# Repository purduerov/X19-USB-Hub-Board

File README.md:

# Purdue ROV X19 USB Hub Board

This board acts as both a PCIe-USB host controller and USB hub board for the ROV stack. In previous years, we had off-the-shelf USB hubs plugged in to the stock ports on the Raspberry Pi. We ran into multiple issues - there were bandwidth allocation issues with the default controller and the hub was just sitting on top of the stack in the enclosure.

The board uses a Renesas uPD720201 USB3.0 host controller to interface with the Raspberry Pi. That takes the PCIe 2.0 x1 interface and makes 4x USB 3.0 ports. Each of those ports (routed 2.0 since 3.0 bandwidth is not required) then go into a USB2422 hub controller and get split into 2 ports, for a total of 8 with 240 Mbps (30 MB/s) dedicated bandwidth.

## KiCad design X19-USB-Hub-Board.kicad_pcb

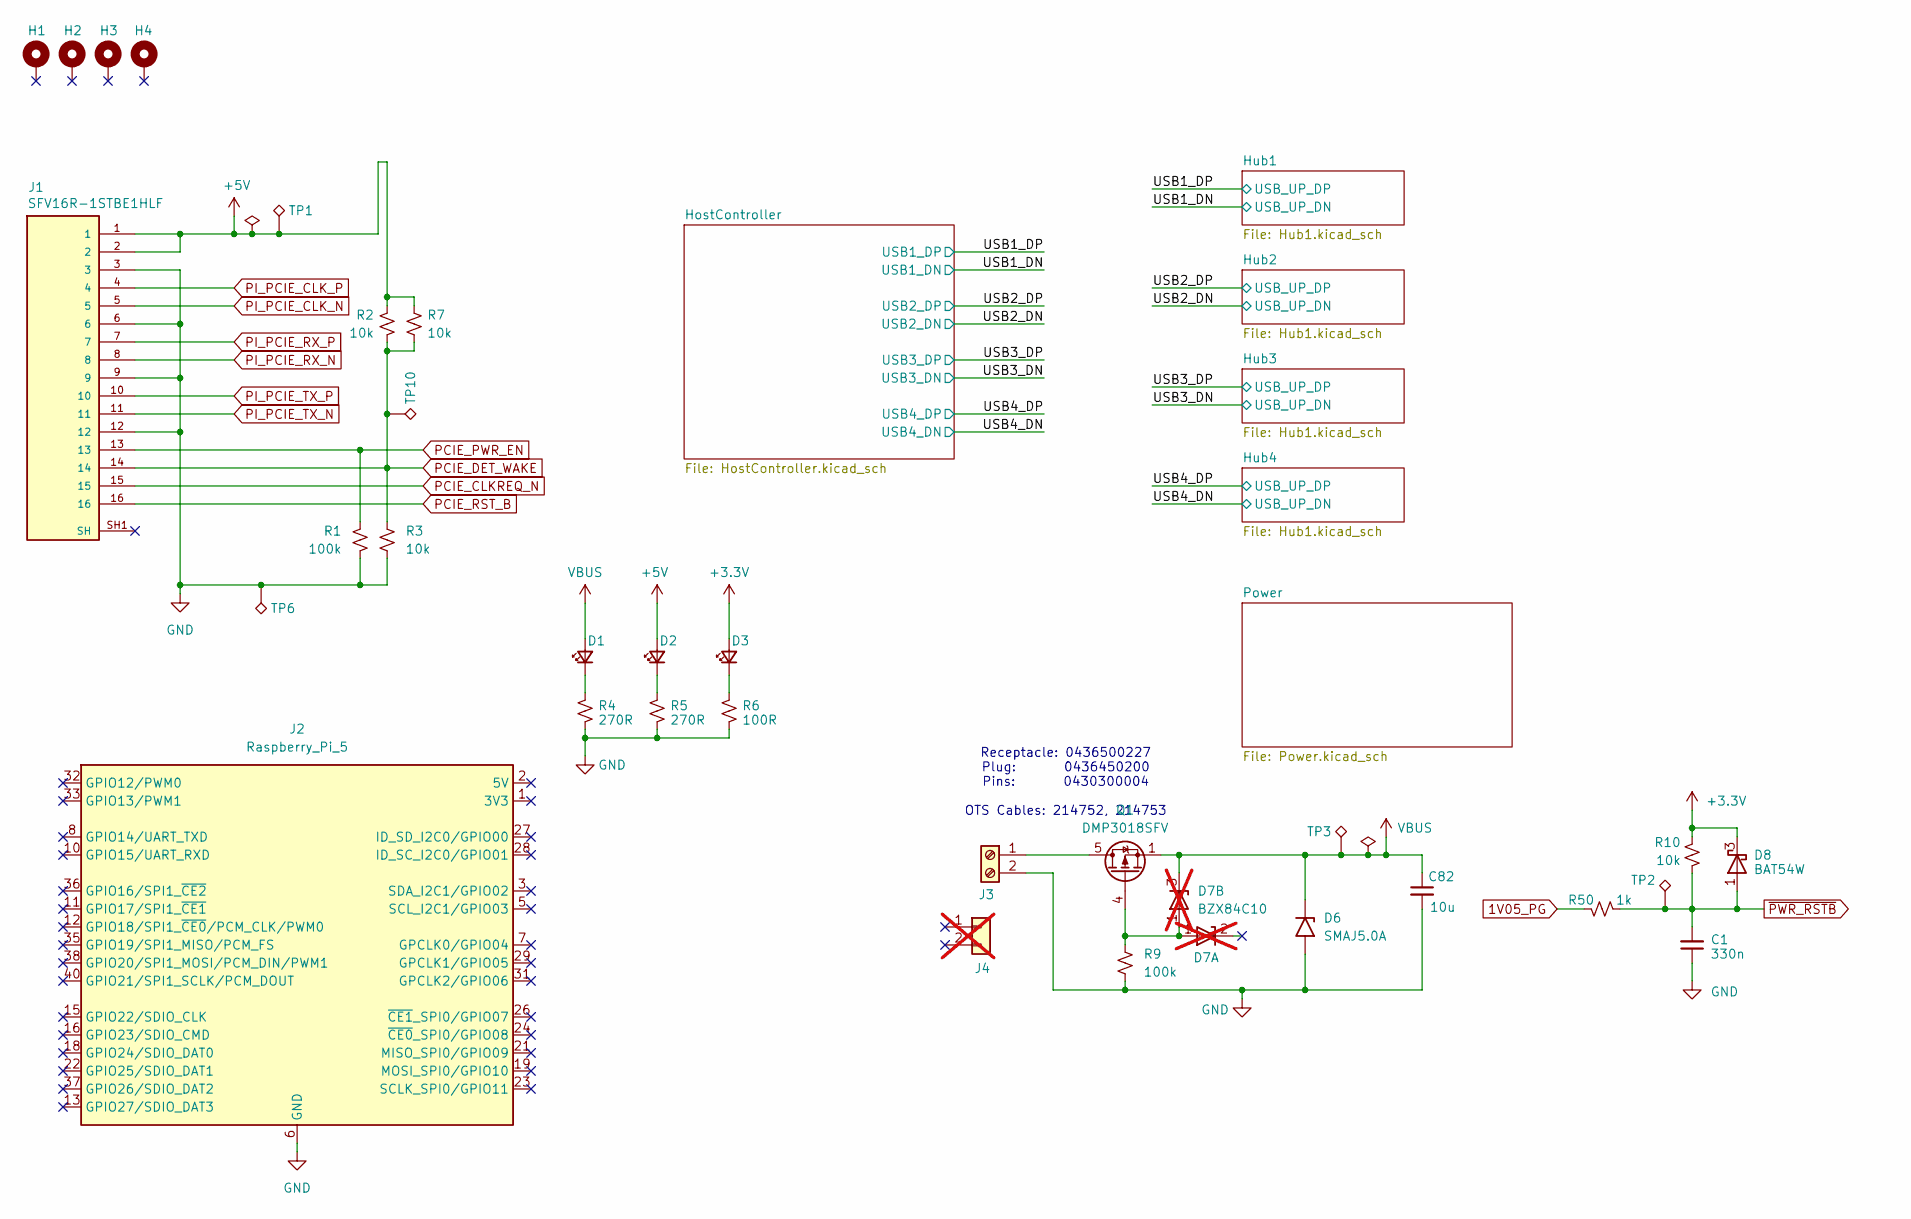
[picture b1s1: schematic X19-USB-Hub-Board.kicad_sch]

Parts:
C1: 330n; C_0402_1005Metric; Part Number CC0402KPX5R6BB334
C82: 10u; C_0805_2012Metric; Part Number CC0805KRX5R8BB106
D1, D2, D3: LED_Small; LED_0603_1608Metric; Part Number LTST-C190GKT
D6: SMAJ5.0A; D_SMA; Part Number SMAJ5.0A
D7: BZX84C10; SOT-23; Part Number BZX84C10; not fitted
D8: BAT54W; SOT-323_SC-70; Part Number BAT54WT-TP
H1, H2, H3, H4: MountingHole_Pad; MountingHole_2.7mm_M2.5_Pad
J1: SFV16R-1STBE1HLF; AMPHENOL_SFV16R-1STBE1HLF; PARTREV B; DigiKey 609-1786-1-ND
J2: Raspberry_Pi_5; PinSocket_2x20_P2.54mm_Vertical; Part Number 1528-1385-ND
J3: 0436500227; Part Number 0436500227
J4: 0436450200; Part Number 0436450200; not fitted
Q1: DMP3018SFV; Diodes_PowerDI3333-8; Part Number DMP3018SFV
R1, R9: 100k; R_0603_1608Metric; Part Number RC0603FR-07100KL
R2, R3, R7, R10: 10k; R_0402_1005Metric; Part Number RC0402FR-0710KL
R4, R5: 270R; R_0603_1608Metric; Part Number RC0603FR-07270RL
R6: 100R; R_0603_1608Metric; Part Number RC0603FR-07100RL
R50: 1k; R_0402_1005Metric; Part Number RC0402FR-071KL
TP1: 5V; TestPoint_Pad_D1.0mm
TP2: ~{PWR_RST}; TestPoint_Pad_D1.0mm
TP3: VBUS; TestPoint_Pad_D1.0mm
TP6: GND; TestPoint_Pad_D1.0mm
TP10: PCIE_DET_WAKE; TestPoint_Pad_D1.0mm

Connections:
1V05_PG: R50.1; also elsewhere on the board
+3.3V: D3.2 (A), D8.3 (K), R10.1; also elsewhere on the board
+5V: D2.2 (A), J1.1, J1.2, R2.1, R7.1, TP1.1 (1_1); also elsewhere on the board
GND: C1.1, C82.2, D6.2 (A2), J1.3, J1.6, J1.9, J1.12, J2.6 (GND), J2.9 (GND), J2.14 (GND), J2.20 (GND), J2.25 (GND), J2.30 (GND), J2.34 (GND), J2.39 (GND), J3.2, R1.2, R3.2, R4.1, R5.1, R6.1, R9.2, TP6.1 (1_1); also elsewhere on the board
unnamed: D1.1 (K), R4.2
unnamed: D2.1 (K), R5.2
unnamed: D3.1 (K), R6.2
unnamed: D7.1 (A), Q1.4 (G), R9.1
unnamed: J3.1, Q1.5 (D)
PCIE_CLKREQ_N: J1.15; also elsewhere on the board
PCIE_DET_WAKE: J1.14, R2.2, R3.1, R7.2, TP10.1 (1_1)
PCIE_PWR_EN: J1.13, R1.1; also elsewhere on the board
PCIE_RST_B: J1.16; also elsewhere on the board
PI_PCIE_CLK_N: J1.5; also elsewhere on the board
PI_PCIE_CLK_P: J1.4; also elsewhere on the board
PI_PCIE_RX_N: J1.8; also elsewhere on the board
PI_PCIE_RX_P: J1.7; also elsewhere on the board
PI_PCIE_TX_N: J1.11; also elsewhere on the board
PI_PCIE_TX_P: J1.10; also elsewhere on the board
VBUS: C82.1, D1.2 (A), D6.1 (A1), D7.3 (K), Q1.1 (S), Q1.2 (S), Q1.3 (S), TP3.1 (1_1); also elsewhere on the board
~PWR_RSTB: C1.2, D8.1 (A), R10.2, R50.2, TP2.1 (1_1); also elsewhere on the board

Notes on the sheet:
Receptacle: 0436500227 Plug: 0436450200 Pins: 0430300004 OTS Cables: 214752, 214753

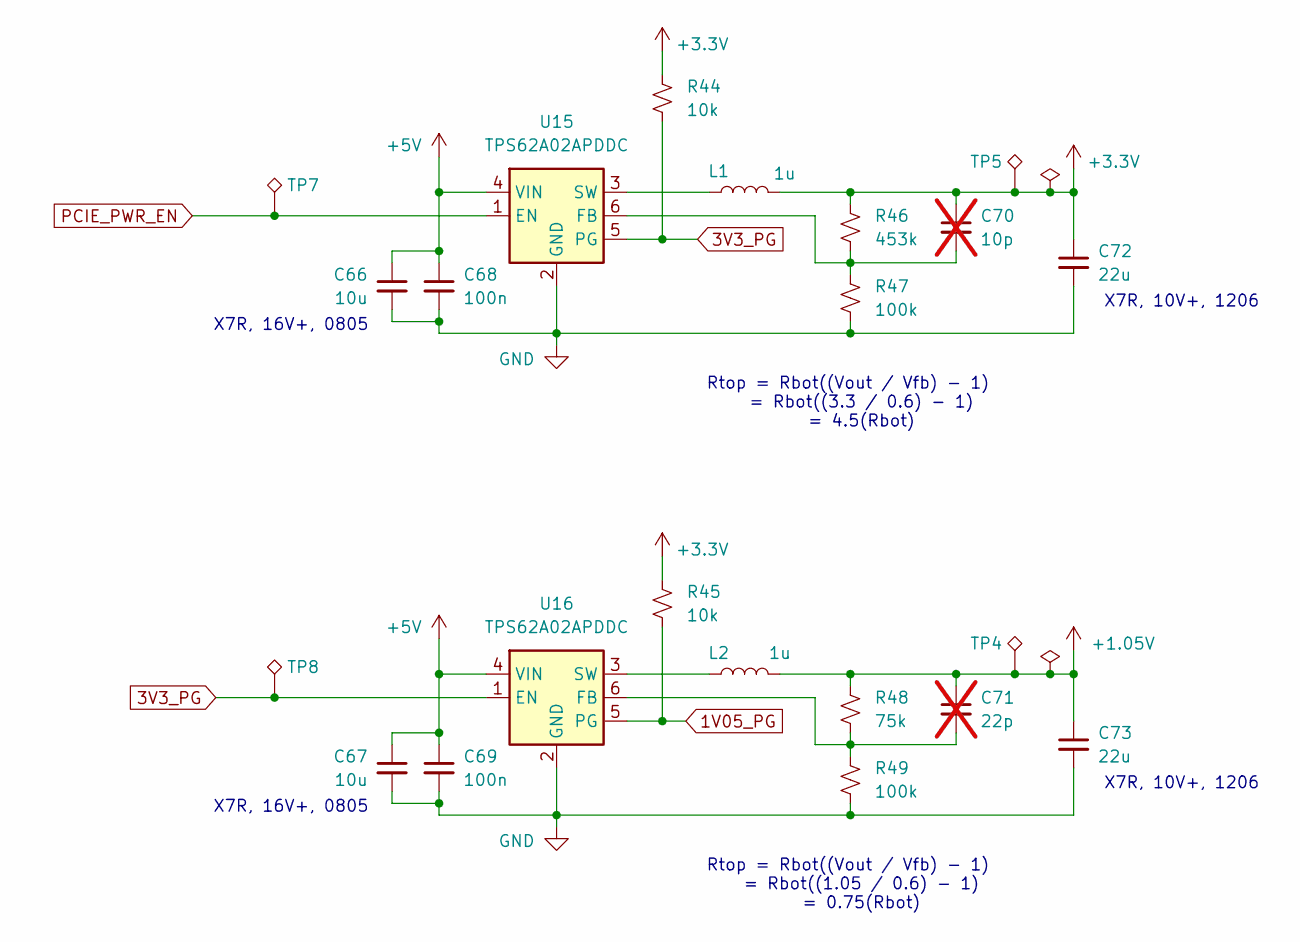
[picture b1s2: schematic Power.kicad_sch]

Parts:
C66, C67: 10u; C_0805_2012Metric; Part Number CC0805KRX5R8BB106
C68, C69: 100n; C_0402_1005Metric; Part Number CC0402KRX7R8BB104
C70: 10p; C_0402_1005Metric; Part Number CC0402JRNPO9BN100; not fitted
C71: 22p; C_0402_1005Metric; Part Number CC0402JRNPO9BN220; not fitted
C72, C73: 22u; C_1206_3216Metric; Part Number CC1206KKX5R8BB226
L1, L2: 1u; L_1008_2520Metric; Part Number DFE252012F-1R0M
R44, R45: 10k; R_0402_1005Metric; Part Number RC0402FR-0710KL
R46: 453k; R_0603_1608Metric; Part Number RC0603FR-07453KL
R47, R49: 100k; R_0603_1608Metric; Part Number RC0603FR-07100KL
R48: 75k; R_0603_1608Metric; Part Number RC0603FR-0775KL
TP4: 1V05; TestPoint_Pad_D1.0mm
TP5: 3V3; TestPoint_Pad_D1.0mm
TP7: PCIE_PWR_EN; TestPoint_Pad_D1.0mm
TP8: 3V3_PG; TestPoint_Pad_D1.0mm
U15, U16: TPS62A02APDDC; SOT-23-6; Part Number TPS62A02APDDCR

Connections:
1V05_PG: R45.2, U16.5 (PG); also elsewhere on the board
3V3_PG: R44.2, TP8.1 (1_1), U15.5 (PG), U16.1 (EN)
+1.05V: C71.1, C73.1, L2.2, R48.1, TP4.1 (1_1); also elsewhere on the board
+3.3V: C70.1, C72.1, L1.2, R44.1, R45.1, R46.1, TP5.1 (1_1); also elsewhere on the board
+5V: C66.1, C67.1, C68.1, C69.1, U15.4 (VIN), U16.4 (VIN); also elsewhere on the board
GND: C66.2, C67.2, C68.2, C69.2, C72.2, C73.2, R47.2, R49.2, U15.2 (GND), U16.2 (GND); also elsewhere on the board
unnamed: C70.2, R46.2, R47.1, U15.6 (FB)
unnamed: L1.1, U15.3 (SW)
unnamed: C71.2, R48.2, R49.1, U16.6 (FB)
unnamed: L2.1, U16.3 (SW)
PCIE_PWR_EN: TP7.1 (1_1), U15.1 (EN); also elsewhere on the board

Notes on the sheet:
X7R, 10V+, 1206
Rtop = Rbot((Vout / Vfb) - 1) = Rbot((1.05 / 0.6) - 1) = 0.75(Rbot)
Rtop = Rbot((Vout / Vfb) - 1) = Rbot((3.3 / 0.6) - 1) = 4.5(Rbot)
X7R, 16V+, 0805

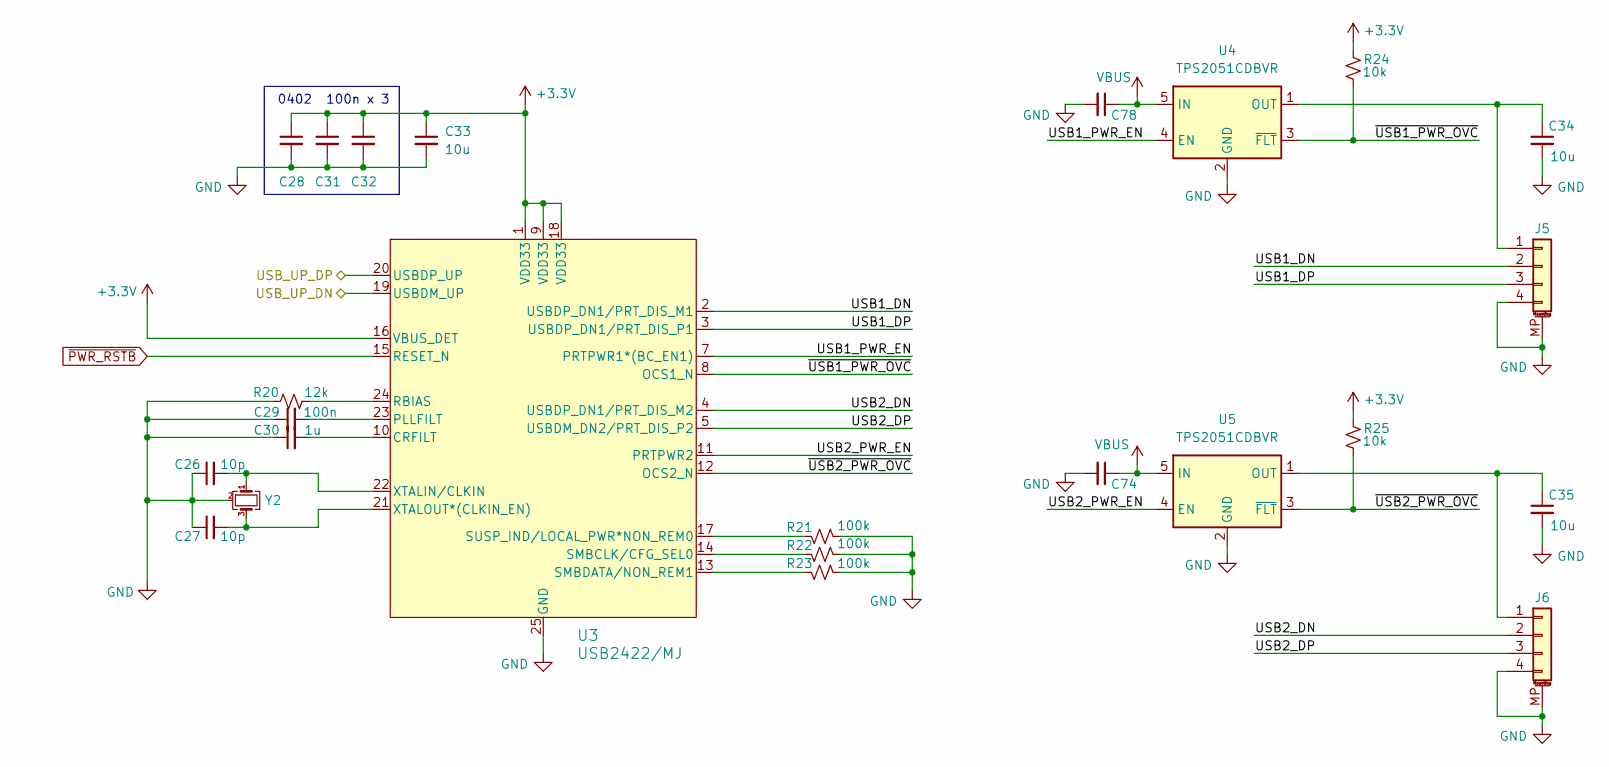
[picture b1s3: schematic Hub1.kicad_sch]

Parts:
C26, C27: 10p; C_0402_1005Metric; Part Number CC0402JRNPO9BN100
C28, C29, C31, C32, C74, C78: 100n; C_0402_1005Metric; Part Number CC0402KRX7R8BB104
C30: 1u; C_0603_1608Metric; Part Number CC0603KRX5R6BB105
C33, C34, C35: 10u; C_0805_2012Metric; Part Number CC0805KRX5R8BB106
J5, J6: BM04B-SRSS-TB; JST_SH_BM04B-SRSS-TB_1x04-1MP_P1.00mm_Vertical; Part Number BM04B-SRSS-TB
R20: 12k; R_0603_1608Metric; Part Number RC0603FR-0712KL
R21, R22, R23: 100k; R_0603_1608Metric; Part Number RC0603FR-07100KL
R24, R25: 10k; R_0402_1005Metric; Part Number RC0402FR-0710KL
U3: USB2422/MJ; QFN-24-1EP_4x4mm_P0.5mm_EP2.5x2.5mm_ThermalVias; Part Number USB2422/MJ; DigiKey USB2422/MJ-ND
U4, U5: TPS2051CDBVR; SOT-23-5; Part Number TPS2051CDBVR
Y2: ECS-240-8-37B-CKY-TR; Crystal_SMD_2016-4Pin_2.0x1.6mm; Part Number ECS-240-8-37B-CKY-TR

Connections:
+3.3V: C28.1, C31.1, C32.1, C33.1, R24.1, R25.1, U3.1 (VDD33), U3.9 (VDD33), U3.16 (VBUS_DET), U3.18 (VDD33); also elsewhere on the board
/Hub1/USB1_DN: J5.2, U3.2 (USBDP_DN1/PRT_DIS_M1)
/Hub1/USB1_DP: J5.3, U3.3 (USBDP_DN1/PRT_DIS_P1)
/Hub1/USB1_PWR_EN: U3.7 (PRTPWR1*(BC_EN1)), U4.4 (EN)
/Hub1/USB2_DN: J6.2, U3.4 (USBDP_DN1/PRT_DIS_M2)
/Hub1/USB2_DP: J6.3, U3.5 (USBDM_DN2/PRT_DIS_P2)
/Hub1/USB2_PWR_EN: U3.11 (PRTPWR2), U5.4 (EN)
/Hub1/~USB1_PWR_OVC: R24.2, U3.8 (OCS1_N), U4.3 (~FLT)
/Hub1/~USB2_PWR_OVC: R25.2, U3.12 (OCS2_N), U5.3 (~FLT)
/USB1_DN: U3.19 (USBDM_UP); also elsewhere on the board
/USB1_DP: U3.20 (USBDP_UP); also elsewhere on the board
GND: C26.1, C27.1, C28.2, C29.1, C30.1, C31.2, C32.2, C33.2, C34.2, C35.2, C74.2, C78.2, J5.4, J5.MP (MountPin), J6.4, J6.MP (MountPin), R20.1, R21.2, R22.2, R23.2, U3.25 (GND), U4.2 (GND), U5.2 (GND), Y2.2 (G), Y2.4 (G); also elsewhere on the board
unnamed: C34.1, J5.1, U4.1 (OUT)
unnamed: C35.1, J6.1, U5.1 (OUT)
unnamed: C30.2, U3.10 (CRFILT)
unnamed: C29.2, U3.23 (PLLFILT)
unnamed: R20.2, U3.24 (RBIAS)
unnamed: R22.1, U3.14 (SMBCLK/CFG_SEL0)
unnamed: R23.1, U3.13 (SMBDATA/NON_REM1)
unnamed: R21.1, U3.17 (SUSP_IND/LOCAL_PWR*NON_REM0)
unnamed: C26.2, U3.22 (XTALIN/CLKIN), Y2.1
unnamed: C27.2, U3.21 (XTALOUT*(CLKIN_EN)), Y2.3
VBUS: C74.1, C78.1, U4.5 (IN), U5.5 (IN); also elsewhere on the board
~PWR_RSTB: U3.15 (RESET_N); also elsewhere on the board

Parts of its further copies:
C36, C37, C46, C47, C56, C57: 10p; C_0402_1005Metric; Part Number CC0402JRNPO9BN100
C38, C39, C41, C42, C48, C49, C51, C52, C58, C59, C61, C62, C75, C76, C77, C79, C80, C81: 100n; C_0402_1005Metric; Part Number CC0402KRX7R8BB104
C40, C50, C60: 1u; C_0603_1608Metric; Part Number CC0603KRX5R6BB105
C43, C44, C45, C53, C54, C55, C63, C64, C65: 10u; C_0805_2012Metric; Part Number CC0805KRX5R8BB106
J7, J8, J9, J10, J11, J12: BM04B-SRSS-TB; JST_SH_BM04B-SRSS-TB_1x04-1MP_P1.00mm_Vertical; Part Number BM04B-SRSS-TB
R26, R32, R38: 12k; R_0603_1608Metric; Part Number RC0603FR-0712KL
R27, R28, R29, R33, R34, R35, R39, R40, R41: 100k; R_0603_1608Metric; Part Number RC0603FR-07100KL
R30, R31, R36, R37, R42, R43: 10k; R_0402_1005Metric; Part Number RC0402FR-0710KL
U6, U9, U12: USB2422/MJ; QFN-24-1EP_4x4mm_P0.5mm_EP2.5x2.5mm_ThermalVias; Part Number USB2422/MJ; DigiKey USB2422/MJ-ND
U7, U8, U10, U11, U13, U14: TPS2051CDBVR; SOT-23-5; Part Number TPS2051CDBVR
Y3, Y4, Y5: ECS-240-8-37B-CKY-TR; Crystal_SMD_2016-4Pin_2.0x1.6mm; Part Number ECS-240-8-37B-CKY-TR

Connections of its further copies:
+3.3V: C38.1, C41.1, C42.1, C43.1, C48.1, C51.1, C52.1, C53.1, C58.1, C61.1, C62.1, C63.1, R30.1, R31.1, R36.1, R37.1, R42.1, R43.1, U6.1 (VDD33), U6.9 (VDD33), U6.16 (VBUS_DET), U6.18 (VDD33), U9.1 (VDD33), U9.9 (VDD33), U9.16 (VBUS_DET), U9.18 (VDD33), U12.1 (VDD33), U12.9 (VDD33), U12.16 (VBUS_DET), U12.18 (VDD33); also elsewhere on the board
/Hub2/USB1_DN: J7.2, U6.2 (USBDP_DN1/PRT_DIS_M1)
/Hub2/USB1_DP: J7.3, U6.3 (USBDP_DN1/PRT_DIS_P1)
/Hub2/USB1_PWR_EN: U6.7 (PRTPWR1*(BC_EN1)), U7.4 (EN)
/Hub2/USB2_DN: J8.2, U6.4 (USBDP_DN1/PRT_DIS_M2)
/Hub2/USB2_DP: J8.3, U6.5 (USBDM_DN2/PRT_DIS_P2)
/Hub2/USB2_PWR_EN: U6.11 (PRTPWR2), U8.4 (EN)
/Hub2/~USB1_PWR_OVC: R30.2, U6.8 (OCS1_N), U7.3 (~FLT)
/Hub2/~USB2_PWR_OVC: R31.2, U6.12 (OCS2_N), U8.3 (~FLT)
/Hub3/USB1_DN: J9.2, U9.2 (USBDP_DN1/PRT_DIS_M1)
/Hub3/USB1_DP: J9.3, U9.3 (USBDP_DN1/PRT_DIS_P1)
/Hub3/USB1_PWR_EN: U9.7 (PRTPWR1*(BC_EN1)), U10.4 (EN)
/Hub3/USB2_DN: J10.2, U9.4 (USBDP_DN1/PRT_DIS_M2)
/Hub3/USB2_DP: J10.3, U9.5 (USBDM_DN2/PRT_DIS_P2)
/Hub3/USB2_PWR_EN: U9.11 (PRTPWR2), U11.4 (EN)
/Hub3/~USB1_PWR_OVC: R36.2, U9.8 (OCS1_N), U10.3 (~FLT)
/Hub3/~USB2_PWR_OVC: R37.2, U9.12 (OCS2_N), U11.3 (~FLT)
/Hub4/USB1_DN: J11.2, U12.2 (USBDP_DN1/PRT_DIS_M1)
/Hub4/USB1_DP: J11.3, U12.3 (USBDP_DN1/PRT_DIS_P1)
/Hub4/USB1_PWR_EN: U12.7 (PRTPWR1*(BC_EN1)), U13.4 (EN)
/Hub4/USB2_DN: J12.2, U12.4 (USBDP_DN1/PRT_DIS_M2)
/Hub4/USB2_DP: J12.3, U12.5 (USBDM_DN2/PRT_DIS_P2)
/Hub4/USB2_PWR_EN: U12.11 (PRTPWR2), U14.4 (EN)
/Hub4/~USB1_PWR_OVC: R42.2, U12.8 (OCS1_N), U13.3 (~FLT)
/Hub4/~USB2_PWR_OVC: R43.2, U12.12 (OCS2_N), U14.3 (~FLT)
/USB2_DN: U6.19 (USBDM_UP); also elsewhere on the board
/USB2_DP: U6.20 (USBDP_UP); also elsewhere on the board
/USB3_DN: U9.19 (USBDM_UP); also elsewhere on the board
/USB3_DP: U9.20 (USBDP_UP); also elsewhere on the board
/USB4_DN: U12.19 (USBDM_UP); also elsewhere on the board
/USB4_DP: U12.20 (USBDP_UP); also elsewhere on the board
GND: C36.1, C37.1, C38.2, C39.1, C40.1, C41.2, C42.2, C43.2, C44.2, C45.2, C46.1, C47.1, C48.2, C49.1, C50.1, C51.2, C52.2, C53.2, C54.2, C55.2, C56.1, C57.1, C58.2, C59.1, C60.1, C61.2, C62.2, C63.2, C64.2, C65.2, C75.2, C76.2, C77.2, C79.2, C80.2, C81.2, J7.4, J7.MP (MountPin), J8.4, J8.MP (MountPin), J9.4, J9.MP (MountPin), J10.4, J10.MP (MountPin), J11.4, J11.MP (MountPin), J12.4, J12.MP (MountPin), R26.1, R27.2, R28.2, R29.2, R32.1, R33.2, R34.2, R35.2, R38.1, R39.2, R40.2, R41.2, U6.25 (GND), U7.2 (GND), U8.2 (GND), U9.25 (GND), U10.2 (GND), U11.2 (GND), U12.25 (GND), U13.2 (GND), U14.2 (GND), Y3.2 (G), Y3.4 (G), Y4.2 (G), Y4.4 (G), Y5.2 (G), Y5.4 (G); also elsewhere on the board
unnamed: C44.1, J7.1, U7.1 (OUT)
unnamed: C45.1, J8.1, U8.1 (OUT)
unnamed: C54.1, J9.1, U10.1 (OUT)
unnamed: C55.1, J10.1, U11.1 (OUT)
unnamed: C64.1, J11.1, U13.1 (OUT)
unnamed: C65.1, J12.1, U14.1 (OUT)
unnamed: C40.2, U6.10 (CRFILT)
unnamed: C39.2, U6.23 (PLLFILT)
unnamed: R26.2, U6.24 (RBIAS)
unnamed: R28.1, U6.14 (SMBCLK/CFG_SEL0)
unnamed: R29.1, U6.13 (SMBDATA/NON_REM1)
unnamed: R27.1, U6.17 (SUSP_IND/LOCAL_PWR*NON_REM0)
unnamed: C36.2, U6.22 (XTALIN/CLKIN), Y3.1
unnamed: C37.2, U6.21 (XTALOUT*(CLKIN_EN)), Y3.3
unnamed: C50.2, U9.10 (CRFILT)
unnamed: C49.2, U9.23 (PLLFILT)
unnamed: R32.2, U9.24 (RBIAS)
unnamed: R34.1, U9.14 (SMBCLK/CFG_SEL0)
unnamed: R35.1, U9.13 (SMBDATA/NON_REM1)
unnamed: R33.1, U9.17 (SUSP_IND/LOCAL_PWR*NON_REM0)
unnamed: C46.2, U9.22 (XTALIN/CLKIN), Y4.1
unnamed: C47.2, U9.21 (XTALOUT*(CLKIN_EN)), Y4.3
unnamed: C60.2, U12.10 (CRFILT)
unnamed: C59.2, U12.23 (PLLFILT)
unnamed: R38.2, U12.24 (RBIAS)
unnamed: R40.1, U12.14 (SMBCLK/CFG_SEL0)
unnamed: R41.1, U12.13 (SMBDATA/NON_REM1)
unnamed: R39.1, U12.17 (SUSP_IND/LOCAL_PWR*NON_REM0)
unnamed: C56.2, U12.22 (XTALIN/CLKIN), Y5.1
unnamed: C57.2, U12.21 (XTALOUT*(CLKIN_EN)), Y5.3
VBUS: C75.1, C76.1, C77.1, C79.1, C80.1, C81.1, U7.5 (IN), U8.5 (IN), U10.5 (IN), U11.5 (IN), U13.5 (IN), U14.5 (IN); also elsewhere on the board
~PWR_RSTB: U6.15 (RESET_N), U9.15 (RESET_N), U12.15 (RESET_N); also elsewhere on the board

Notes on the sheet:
0402
100n x 3

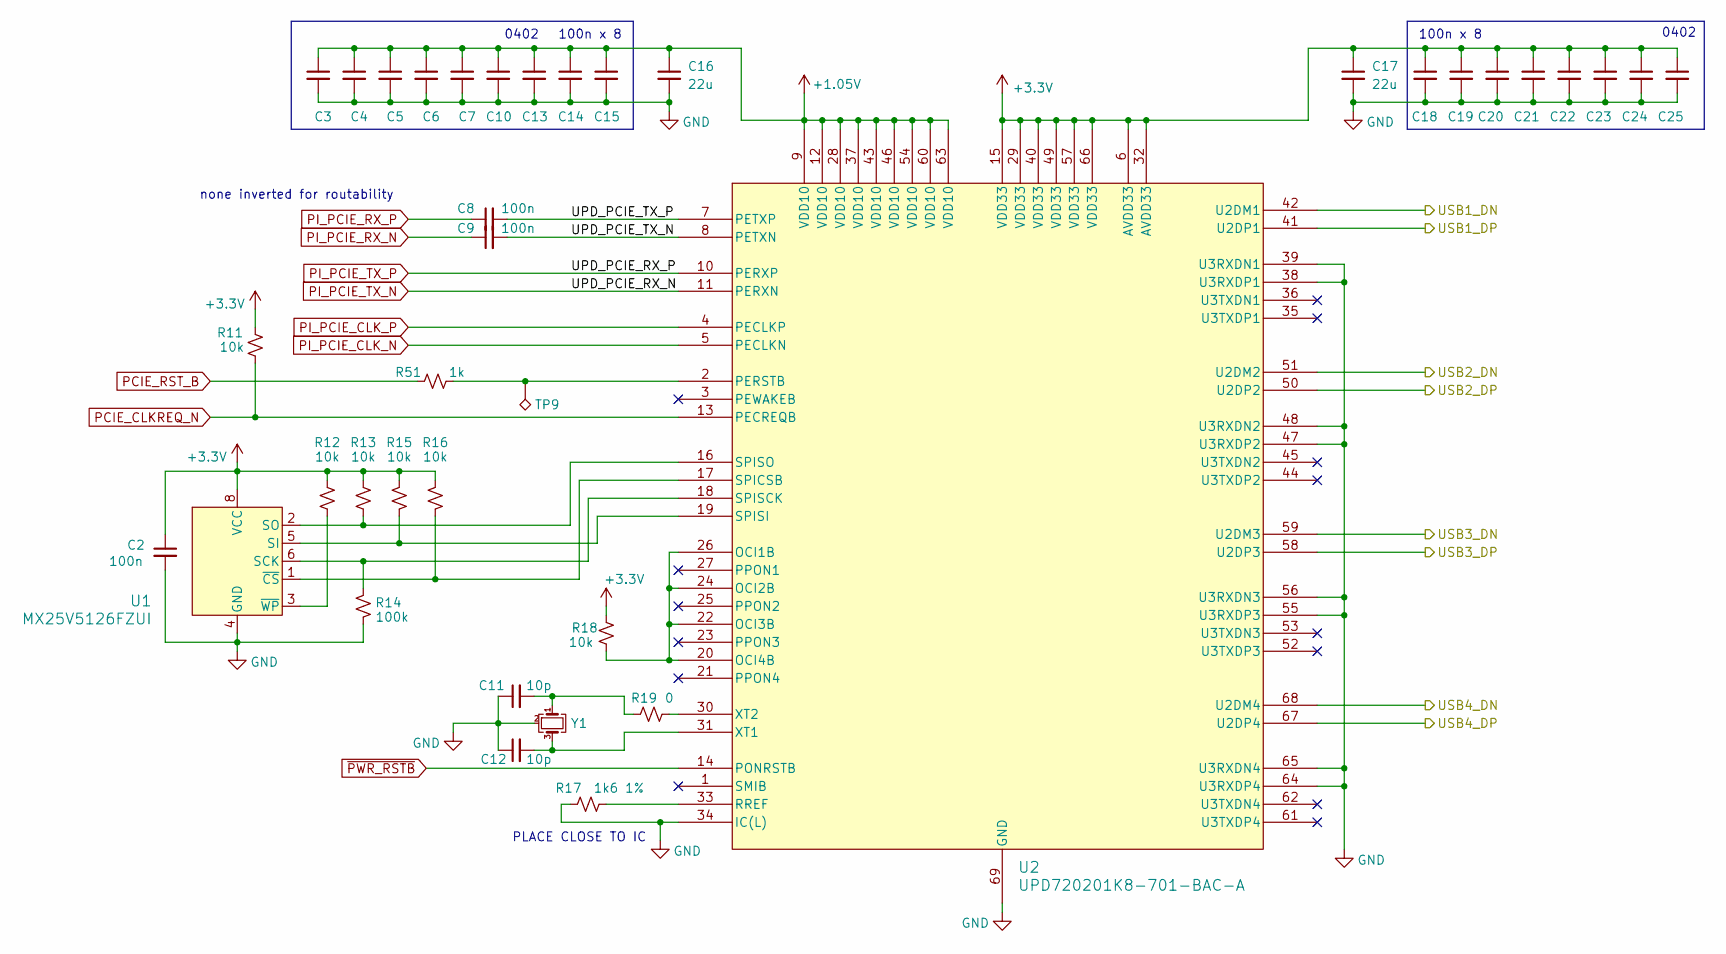
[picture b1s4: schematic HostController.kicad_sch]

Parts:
C2, C3, C4, C5, C6, C7, C8, C9, C10, C13, C14, C15, C18, C19, C20, C21, C22, C23, C24, C25: 100n; C_0402_1005Metric; Part Number CC0402KRX7R8BB104
C11, C12: 10p; C_0402_1005Metric; Part Number CC0402JRNPO9BN100
C16, C17: 22u; C_1206_3216Metric; Part Number CC1206KKX5R8BB226
R11, R12, R13, R15, R16, R18: 10k; R_0402_1005Metric; Part Number RC0402FR-0710KL
R14: 100k; R_0603_1608Metric; Part Number RC0603FR-07100KL
R17: 1k6 1%; R_0603_1608Metric; Part Number RC0603FR-071K6L
R19: 0; R_0402_1005Metric; Part Number RC0402FR-070RL
R51: 1k; R_0402_1005Metric; Part Number RC0402FR-071KL
TP9: PCIE_RST; TestPoint_Pad_D1.0mm
U1: MX25V5126FZUI; Winbond_USON-8-1EP_3x2mm_P0.5mm_EP0.2x1.6mm; Part Number MX25V5126FZUI; DigiKey 1092-1065-1-ND
U2: UPD720201K8-701-BAC-A; QFN-68-1EP_8x8mm_P0.4mm_EP6.2x6.2mm; Part Number UPD720201K8-701-BAC-A; DigiKey UPD720201K8-701-BAC-A-ND
Y1: ECS-240-8-37B-CKY-TR; Crystal_SMD_2016-4Pin_2.0x1.6mm; Part Number ECS-240-8-37B-CKY-TR

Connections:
+1.05V: C3.1, C4.1, C5.1, C6.1, C7.1, C10.1, C13.1, C14.1, C15.1, C16.1, U2.9 (VDD10), U2.12 (VDD10), U2.28 (VDD10), U2.37 (VDD10), U2.43 (VDD10), U2.46 (VDD10), U2.54 (VDD10), U2.60 (VDD10), U2.63 (VDD10); also elsewhere on the board
+3.3V: C2.1, C17.1, C18.1, C19.1, C20.1, C21.1, C22.1, C23.1, C24.1, C25.1, R11.1, R12.1, R13.1, R15.1, R16.1, R18.1, U1.8 (VCC), U2.6 (AVDD33), U2.15 (VDD33), U2.29 (VDD33), U2.32 (AVDD33), U2.40 (VDD33), U2.49 (VDD33), U2.57 (VDD33), U2.66 (VDD33); also elsewhere on the board
/HostController/UPD_PCIE_TX_N: C9.2, U2.8 (PETXN)
/HostController/UPD_PCIE_TX_P: C8.2, U2.7 (PETXP)
/USB1_DN: U2.42 (U2DM1); also elsewhere on the board
/USB1_DP: U2.41 (U2DP1); also elsewhere on the board
/USB2_DN: U2.51 (U2DM2); also elsewhere on the board
/USB2_DP: U2.50 (U2DP2); also elsewhere on the board
/USB3_DN: U2.59 (U2DM3); also elsewhere on the board
/USB3_DP: U2.58 (U2DP3); also elsewhere on the board
/USB4_DN: U2.68 (U2DM4); also elsewhere on the board
/USB4_DP: U2.67 (U2DP4); also elsewhere on the board
GND: C2.2, C3.2, C4.2, C5.2, C6.2, C7.2, C10.2, C11.1, C12.1, C13.2, C14.2, C15.2, C16.2, C17.2, C18.2, C19.2, C20.2, C21.2, C22.2, C23.2, C24.2, C25.2, R14.2, R17.1, U1.4 (GND), U1.9 (EP), U2.34 (IC(L)), U2.38 (U3RXDP1), U2.39 (U3RXDN1), U2.47 (U3RXDP2), U2.48 (U3RXDN2), U2.55 (U3RXDP3), U2.56 (U3RXDN3), U2.64 (U3RXDP4), U2.65 (U3RXDN4), U2.69 (GND), Y1.2 (G), Y1.4 (G); also elsewhere on the board
unnamed: C11.2, R19.1, Y1.1
unnamed: R14.1, U1.6 (SCK), U2.18 (SPISCK)
unnamed: R15.2, U1.5 (SI), U2.19 (SPISI)
unnamed: R13.2, U1.2 (SO), U2.16 (SPISO)
unnamed: R16.2, U1.1 (~CS), U2.17 (SPICSB)
unnamed: R12.2, U1.3 (~WP)
unnamed: R18.2, U2.20 (OCI4B), U2.22 (OCI3B), U2.24 (OCI2B), U2.26 (OCI1B)
unnamed: R51.2, TP9.1 (1_1), U2.2 (PERSTB)
unnamed: R17.2, U2.33 (RREF)
unnamed: C12.2, U2.31 (XT1), Y1.3
unnamed: R19.2, U2.30 (XT2)
PCIE_CLKREQ_N: R11.2, U2.13 (PECREQB); also elsewhere on the board
PCIE_RST_B: R51.1; also elsewhere on the board
PI_PCIE_CLK_N: U2.5 (PECLKN); also elsewhere on the board
PI_PCIE_CLK_P: U2.4 (PECLKP); also elsewhere on the board
PI_PCIE_RX_N: C9.1; also elsewhere on the board
PI_PCIE_RX_P: C8.1; also elsewhere on the board
PI_PCIE_TX_N: U2.11 (PERXN); also elsewhere on the board
PI_PCIE_TX_P: U2.10 (PERXP); also elsewhere on the board
~PWR_RSTB: U2.14 (PONRSTB); also elsewhere on the board

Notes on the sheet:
100n x 8
0402
none inverted for routability
PLACE CLOSE TO IC

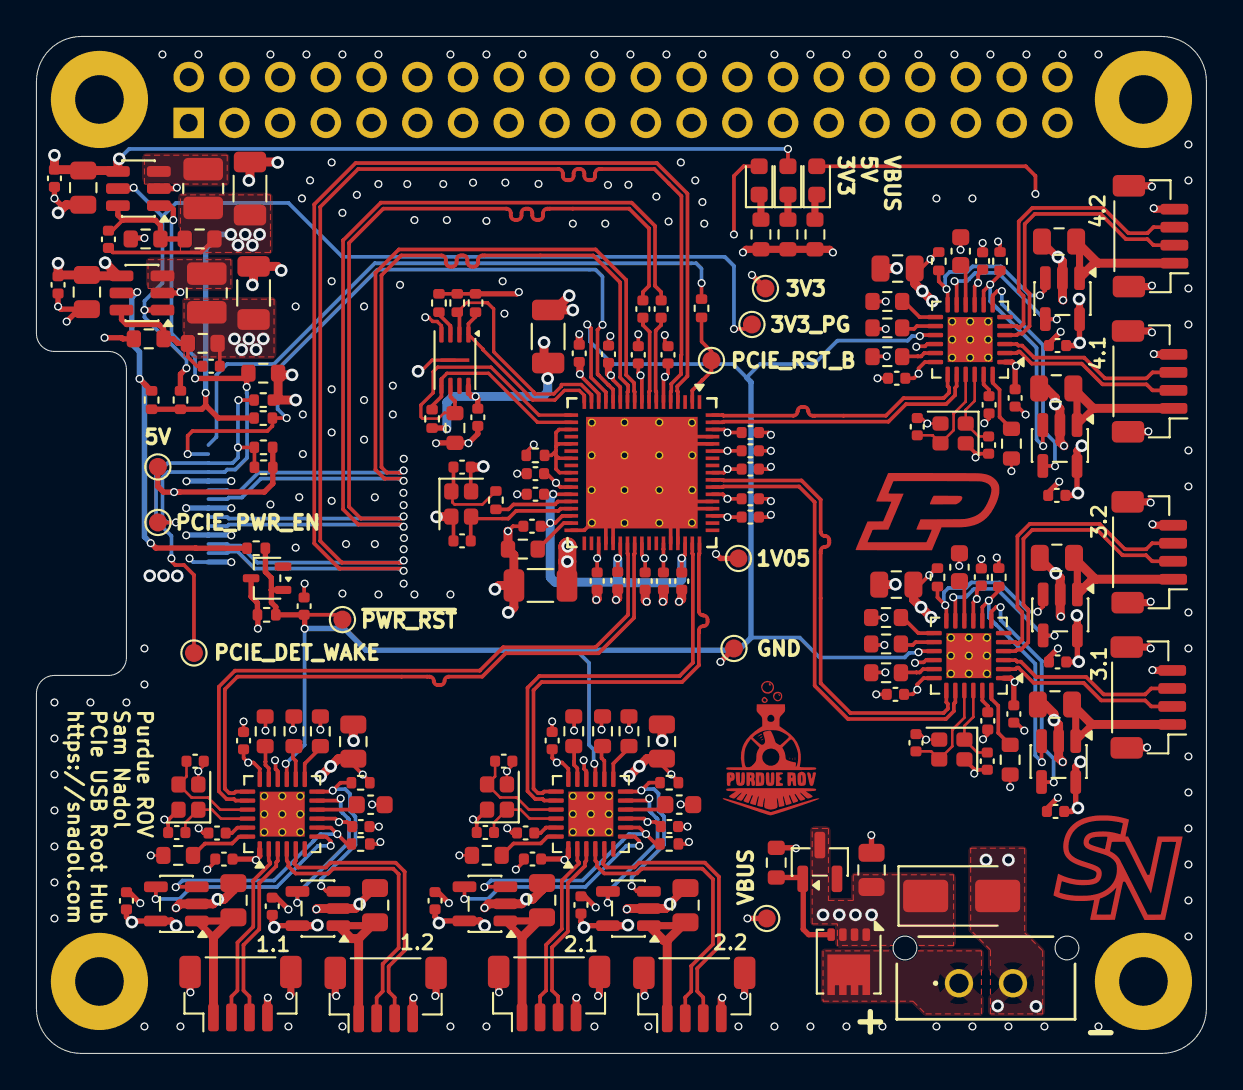
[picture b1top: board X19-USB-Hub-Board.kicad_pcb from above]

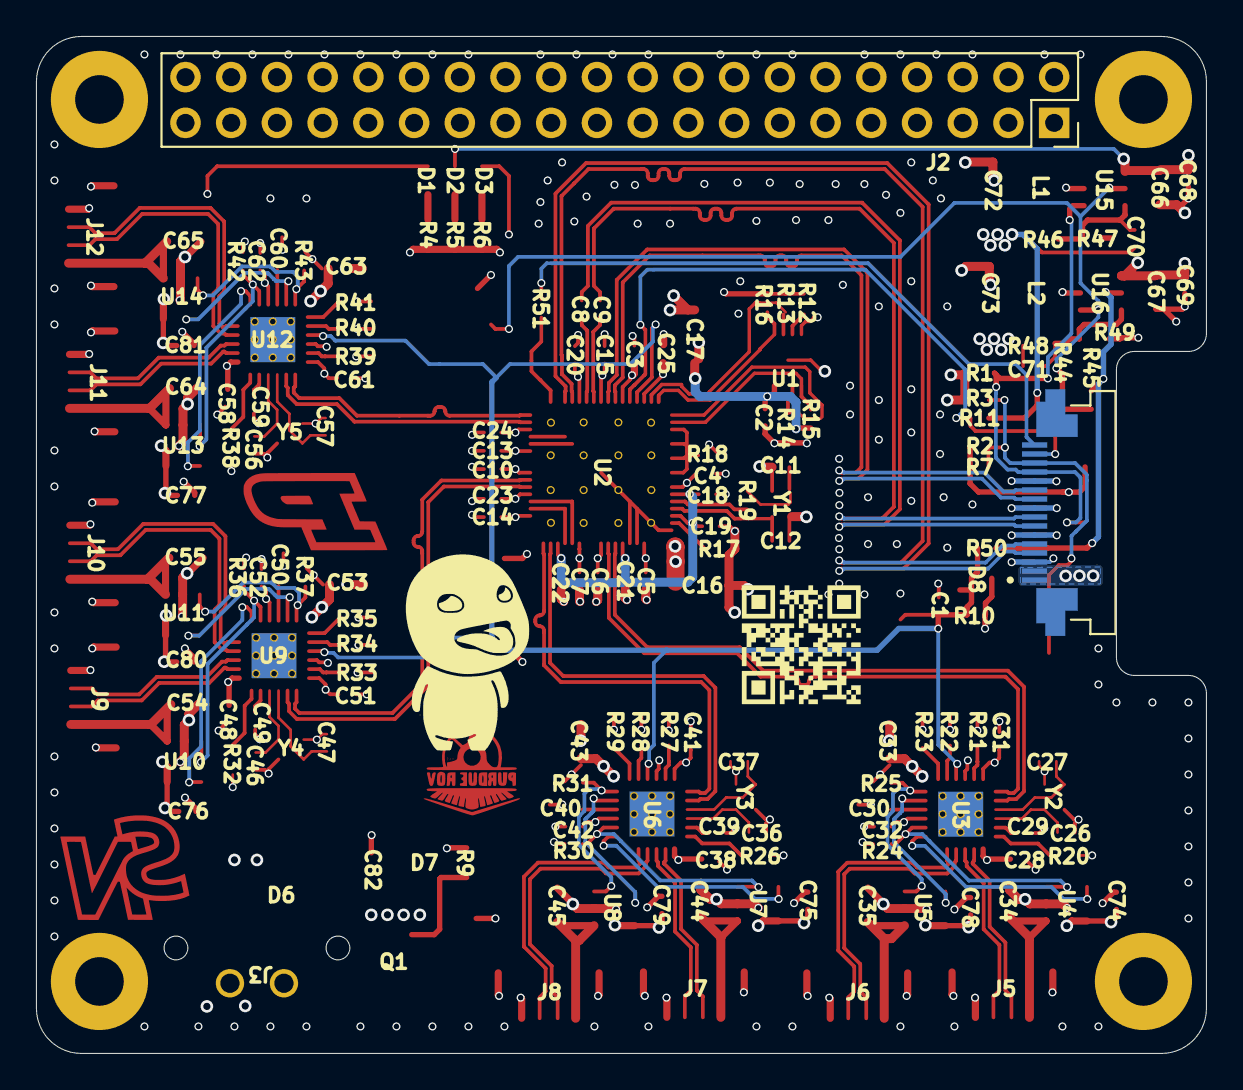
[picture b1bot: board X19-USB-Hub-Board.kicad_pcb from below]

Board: 4 copper layers, 65.0 x 56.5 mm, 187 parts (2 on the bottom side), 120 nets.

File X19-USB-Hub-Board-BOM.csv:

Row,Description,Part,References,Value,Footprint,Quantity Per PCB,Status,Datasheet,Sim.Pins,Part Number,KLC_S3.3,KLC_S4.1,PARTREV,MANUFACTURER,MAXIMUM_PACKAGE_HEIGHT,STANDARD,MPN,DigiKey,Temp_Range,Category,Verified
1,"Unpolarized capacitor, small symbol",C_Small,C11 C12 C26 C27 C36 C37 C46 C47 C56 C57,10p,C_0402_1005Metric,10, ,,,CC0402JRNPO9BN100,,,,,,,,,,,
2,"Unpolarized capacitor, small symbol",C_Small,C2 C3 C4 C5 C6 C7 C8 C9 C10 C13 C14 C15 C18 C19 C20 C21 C22 C23 C24 C25 C28 C29 C31 C32 C38 C39 C41 C42 C48 C49 C51 C52 C58 C59 C61 C62 C68 C69,100n,C_0402_1005Metric,38, ,,,CC0402KRX7R8BB104,,,,,,,,,,,
3,"Unpolarized capacitor, small symbol",C_Small,C1,330n,C_0402_1005Metric,1, ,,,CC0402KPX5R6BB334,,,,,,,,,,,
4,"Unpolarized capacitor, small symbol",C_Small,C30 C40 C50 C60,1u,C_0603_1608Metric,4, ,,,CC0603KRX5R6BB105,,,,,,,,,,,
5,"Unpolarized capacitor, small symbol",C_Small,C33 C34 C35 C43 C44 C45 C53 C54 C55 C63 C64 C65 C66 C67,10u,C_0805_2012Metric,14, ,,,CC0805KRX5R8BB106,,,,,,,,,,,
6,"Unpolarized capacitor, small symbol",C_Small,C16 C17 C72 C73,22u,C_1206_3216Metric,4, ,,,CC1206KKX5R8BB226,,,,,,,,,,,
7,"Schottky barrier diode, SOT-323",BAT54W,D8,BAT54W,SOT-323_SC-70,1, ,https://assets.nexperia.com/documents/data-sheet/BAT54W_SER.pdf,,BAT54W,,,,,,,,,,,
8,"Light emitting diode, small symbol",LED_Small,D1 D2 D3 D4 D5,LED_Small,LED_0603_1608Metric,5, ,,1=K 2=A,LTST-C190GKT,,,,,,,,,,,
9,"400W unidirectional Transient Voltage Suppressor, 5.0Vr, SMA(DO-214AC)",SMAJ5.0A,D6,SMAJ5.0A,D_SMA,1, ,https://www.littelfuse.com/media?resourcetype=datasheets&ite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,,SMAJ5.0A,,,,,,,,,,,
10,"Generic screw terminal, single row, 01x02, script generated (kicad-library-utils/schlib/autogen/connector/)",Screw_Terminal_01x02,J3,0436500227,0436500227,1, ,,,1053131102,,,,,,,,,,,
11,"Generic connectable mounting pin connector, single row, 01x04, script generated (kicad-library-utils/schlib/autogen/connector/)",Conn_01x04_MountingPin,J5 J6 J7 J8 J9 J10 J11 J12,BM04B-SRSS-TB,JST_SH_BM04B-SRSS-TB_1x04-1MP_P1.00mm_Vertical,8, ,,,BM04B-SRSS-TB,,,,,,,,,,,
12,"FFC/FPC Connector, 0.50mm Pitch, Right-Angle, 16 Circuits, Top Contact",SFV16R-1STBE1HLF,J1,SFV16R-1STBE1HLF,AMPHENOL_SFV16R-1STBE1HLF,1, ,https://www.amphenol-cs.com/media/wysiwyg/files/drawing/sfv_r.pdf,,SFV16R-1STBE1HLF,,,B,Amphenol FCI Amphenol ICC (FCI),2.0mm,Manufacturer Recommendations,SFV16R-1STBE1HLF,609-1786-1-ND,-55°C to 105°C,Connectors,Yes
13,Inductor,L,L1 L2,1u,L_1008_2520Metric,2, ,,,DFE252012F-1R0M,,,,,,,,,,,
14,"-12A Id, -30V Vds, P-Channel Power MOSFET, 9.5mOhm Ron, 33.7nC Qg (typ), PowerDI3333-8",DMP3013SFV,Q1,DMP3018SFV,Diodes_PowerDI3333-8,1, ,https://www.diodes.com/assets/Datasheets/DMP3013SFV.pdf,,DMP3018SFV,,,,,,,,,,,
15,"Resistor, small US symbol",R_Small_US,R19,0,R_0402_1005Metric,1, ,,,RC0402FR-070RL,,,,,,,,,,,
16,"Resistor, small US symbol",R_Small_US,R6 R7 R8,100R,R_0603_1608Metric,3, ,,,RC0603FR-07100RL,,,,,,,,,,,
17,"Resistor, small US symbol",R_Small_US,R4 R5,270R,R_0603_1608Metric,2, ,,,RC0603FR-07270RL,,,,,,,,,,,
18,"Resistor, small US symbol",R_Small_US,R17,1k6 1%,R_0603_1608Metric,1, ,,,RC0603FR-071K6L,,,,,,,,,,,
19,"Resistor, small US symbol",R_Small_US,R2,5k1,R_0603_1608Metric,1, ,,,RC0603FR-075K1L,,,,,,,,,,,
20,"Resistor, small US symbol",R_Small_US,R3 R10 R11 R12 R13 R15 R16 R18 R24 R25 R30 R31 R36 R37 R42 R43 R44 R45,10k,R_0402_1005Metric,18, ,,,RC0402FR-0710KL,,,,,,,,,,,
21,"Resistor, small US symbol",R_Small_US,R20 R26 R32 R38,12k,R_0603_1608Metric,4, ,,,RC0603FR-0712KL,,,,,,,,,,,
22,"Resistor, small US symbol",R_Small_US,R48,75k,R_0603_1608Metric,1, ,,,RC0603FR-0775KL,,,,,,,,,,,
23,"Resistor, small US symbol",R_Small_US,R1 R9 R14 R21 R22 R23 R27 R28 R29 R33 R34 R35 R39 R40 R41 R47 R49,100k,R_0603_1608Metric,17, ,,,RC0603FR-07100KL,,,,,,,,,,,
24,"Resistor, small US symbol",R_Small_US,R46,453k,R_0603_1608Metric,1, ,,,RC0603FR-07453KL,,,,,,,,,,,
25,"512Kb (64K x 8) Serial NOR Flash Memory, SPI, 8-USON",MX25V5126FZUI,U1,MX25V5126FZUI,Winbond_USON-8-1EP_3x2mm_P0.5mm_EP0.2x1.6mm,1, ,"https://www.macronix.com/Lists/Datasheet/Attachments/7434/MX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,%202.5V-3.6V,%20512Kb,%20v1.1.pdf",,MX25V5126FZUI,,,,Macronix,,,MX25V5126FZUI,1092-1065-1-ND,-40°C to 85°C,Logic,Yes
26,"0.5A Current limited power switch, single channel, output discharge, reverse blocking, SOT-23-5",TPS2051CDBV,U4 U5 U7 U8 U10 U11 U13 U14,TPS2051CDBVR,SOT-23-5,8, ,https://www.ti.com/lit/ds/symlink/tps2051c.pdf,,TPS2051CDBVR,,,,,,,,,,,
27,"High Efficiency Synchronous Buck Converter with forced PWM, Adjustable Output 0.6V-5.5V, 2A, Power Good, Enable, SOT-23-6",TPS62A02APDDC,U15 U16,TPS62A02APDDC,SOT-23-6,2, ,https://www.ti.com/lit/gpn/tps62a02a,,TPS62A02APDDC,,,,,,,,,,,
28,"USB 3.0 Host Controller, 4 Ports, PCIe to USB 3.0, 68-QFN",UPD720201K8-7x1-BAC-A,U2,UPD720201K8-7x1-BAC-A,QFN-68-1EP_8x8mm_P0.4mm_EP6.2x6.2mm,1, ,https://www.renesas.com/en/document/dst/upd720201-upd720202-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,,UPD720201K8-701-BAC-A,,,,Renesas Electronics Corporation,,,UPD720201K8-711-BAC-A,UPD720201K8-711-BAC-ACT-ND,0°C to 85°C,Logic,Yes
29,"2-Port USB 2.0 Hi-Speed Hub Controller, 24-QFN",USB2422_MJ,U3 U6 U9 U12,USB2422/MJ,QFN-24-1EP_4x4mm_P0.5mm_EP2.5x2.5mm_ThermalVias,4, ,https://ww1.microchip.com/downloads/en/DeviceDoc/00000062A.pdf,,USB2422/MJ,,,,Microchip Technology,,,USB2422/MJ,USB2422/MJ-ND,0°C to 70°C,Logic,Yes
30,"Four pin crystal, GND on pins 2 and 4, small symbol",Crystal_GND24_Small,Y1 Y2 Y3 Y4 Y5,ECS-240-8-37B-CKY-TR,Crystal_SMD_2016-4Pin_2.0x1.6mm,5, ,,,ECS-240-8-37B-CKY-TR,The rectangle is not a symbol body but a graphical element,Some pins are on 50mil grid to make the symbol small,,,,,,,,,





Project info:
Schematic:,X19-USB-Hub-Board
Variant:,default
Revision:,
Date:,2026-10-12_05-40-34
KiCad Version:,10.0.5-unknown-202607221313~667fa36054~ubuntu25.10.1
Statistics:
Component Groups:,30
Component Count:,161
Fitted Components:,161
Number of PCBs:,1
Total Components:,161
